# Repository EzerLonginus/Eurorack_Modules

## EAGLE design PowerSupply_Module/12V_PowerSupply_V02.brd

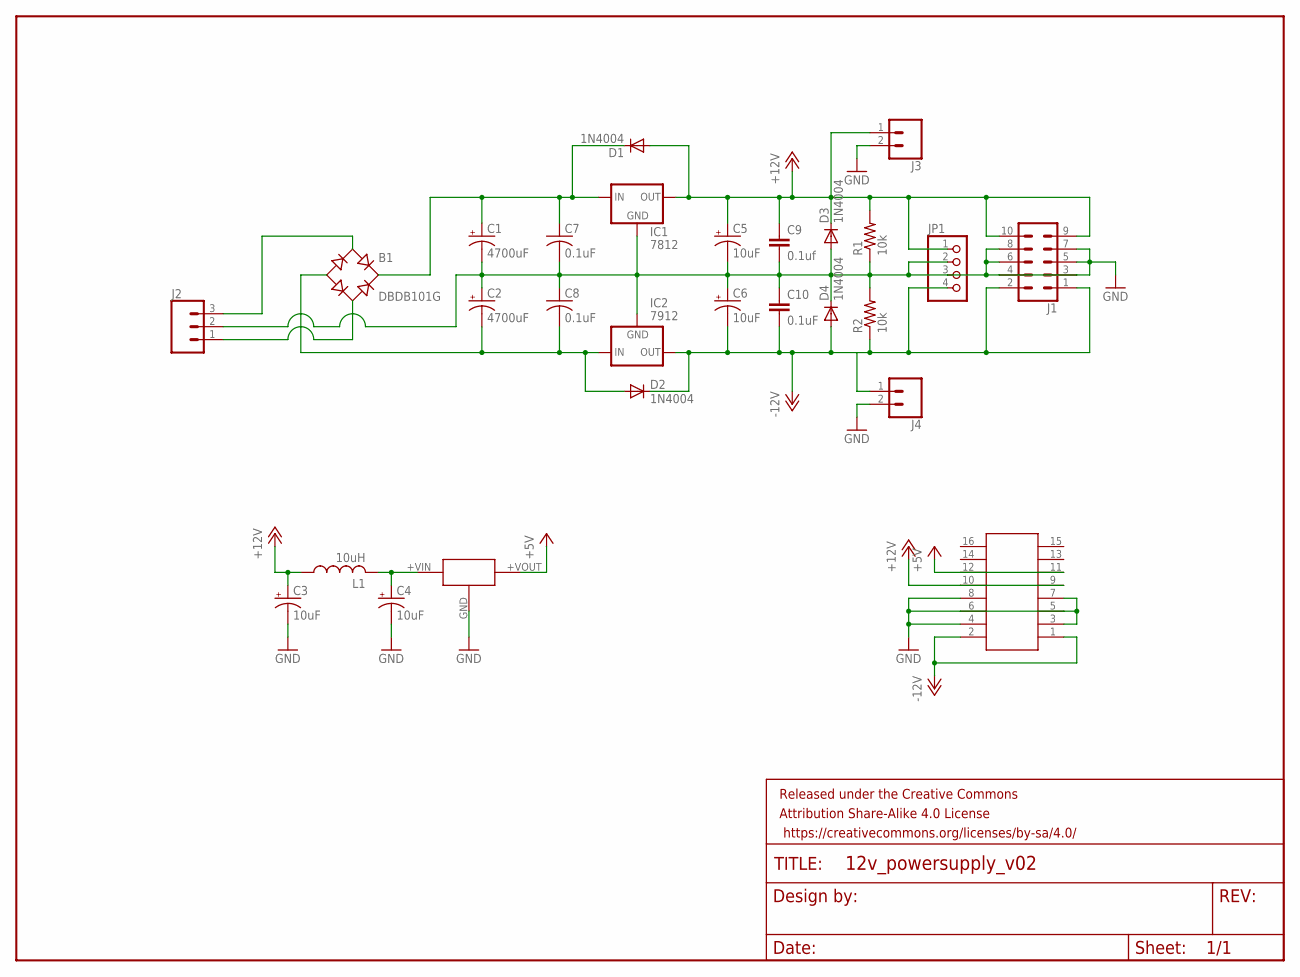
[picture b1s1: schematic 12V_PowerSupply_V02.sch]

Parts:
B1: DBDB101G; DB
C1, C2: 4700uF; E7,5-18
C3, C4, C5, C6: 10uF; E2,5-7
C7, C8: 0.1uF; C150-054X183
C9: 0.1uf; C050-025X075
C10: 0.1uF; C050-025X075
D1, D2, D3, D4: 1N4004; DO41-10
FRAME1: FRAME-LETTER; CREATIVE_COMMONS
IC1: 7812; 78XXS
IC2: 7912; 79XXS
J1: CONN_05X2SHD; 2X5-SHROUDED
J2: CONN_03-SCREW-5MM; SCREWTERMINAL-5MM-3
J3, J4: CONN_023.5MM-NO_SILK; SCREWTERMINAL-3.5MM-2-NS
JP1: PINHD-1X4; 1X04
L1: 10uH; 6000-XXXX-RC
R1, R2: 10k; 0204/7
U$1: 8X2_HEADER_SHROUDED
U$2: R_78E_5V; R_78E

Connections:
+5V: U$1.11, U$1.12, U$2.+VOUT
+12V: C3.+, C5.+, C9.1, D1.A, D3.C, IC1.OUT, J1.9, J1.10, J3.1, JP1.1, L1.1, R1.2, U$1.9, U$1.10
-12V: C6.-, C10.2, D2.C, D4.A, IC2.OUT, J1.1, J1.2, J4.1, JP1.4, R2.1, U$1.1, U$1.2
GND: C1.-, C2.+, C3.-, C4.-, C5.-, C6.+, C7.2, C8.1, C9.2, C10.1, D3.A, D4.C, IC1.GND, IC2.GND, J1.3, J1.4, J1.5, J1.6, J1.7, J1.8, J2.2, J3.2, J4.2, JP1.2, JP1.3, R1.1, R2.2, U$1.3, U$1.4, U$1.5, U$1.6, U$1.7, U$1.8, U$2.GND
unnamed: C4.+, L1.2, U$2.+VIN
unnamed: B1.+, C1.+, C7.1, D1.C, IC1.IN
unnamed: B1.-, C2.-, C8.2, D2.A, IC2.IN
unnamed: B1.AC1, J2.3
unnamed: B1.AC2, J2.1

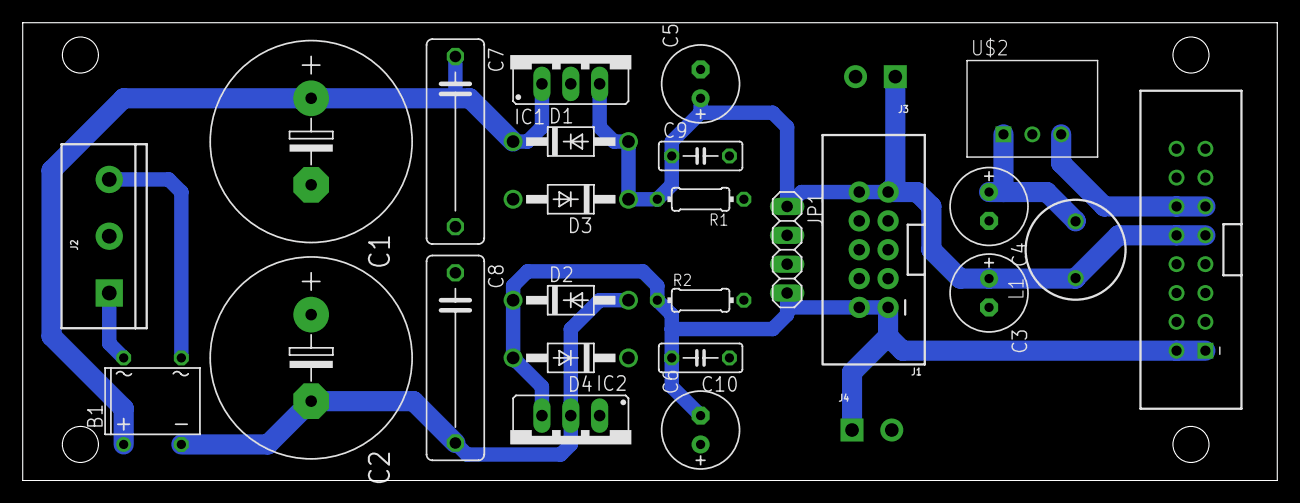
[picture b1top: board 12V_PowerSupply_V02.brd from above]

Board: 2 copper layers, 110.5 x 40.3 mm, 28 parts (0 on the bottom side), 9 nets.

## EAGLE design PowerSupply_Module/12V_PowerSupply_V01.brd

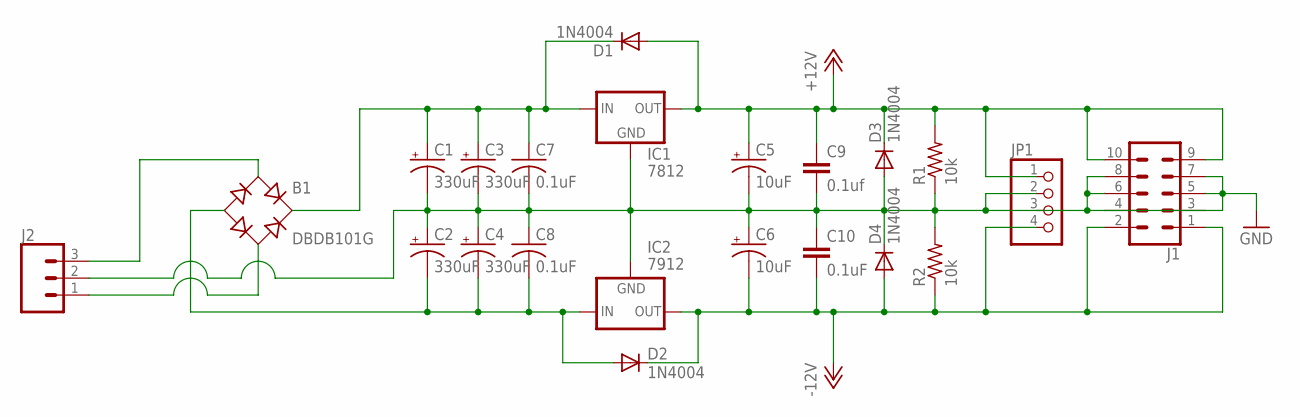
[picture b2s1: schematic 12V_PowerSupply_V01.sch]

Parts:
B1: DBDB101G; DB
C1, C2, C3, C4: 330uF; E7,5-18
C5, C6: 10uF; E2,5-7
C7, C8: 0.1uF; C150-054X183
C9: 0.1uf; C050-025X075
C10: 0.1uF; C050-025X075
D1, D2, D3, D4: 1N4004; DO41-10
IC1: 7812; 78XXS
IC2: 7912; 79XXS
J1: CONN_05X2SHD; 2X5-SHROUDED
J2: CONN_03-SCREW-5MM; SCREWTERMINAL-5MM-3
JP1: PINHD-1X4; 1X04
R1, R2: 10k; 0204/7

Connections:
+12V: C5.+, C9.1, D1.A, D3.C, IC1.OUT, J1.9, J1.10, JP1.1, R1.2
-12V: C6.-, C10.2, D2.C, D4.A, IC2.OUT, J1.1, J1.2, JP1.4, R2.1
GND: C1.-, C2.+, C3.-, C4.+, C5.-, C6.+, C7.2, C8.1, C9.2, C10.1, D3.A, D4.C, IC1.GND, IC2.GND, J1.3, J1.4, J1.5, J1.6, J1.7, J1.8, J2.2, JP1.2, JP1.3, R1.1, R2.2
unnamed: B1.+, C1.+, C3.+, C7.1, D1.C, IC1.IN
unnamed: B1.-, C2.-, C4.-, C8.2, D2.A, IC2.IN
unnamed: B1.AC1, J2.3
unnamed: B1.AC2, J2.1

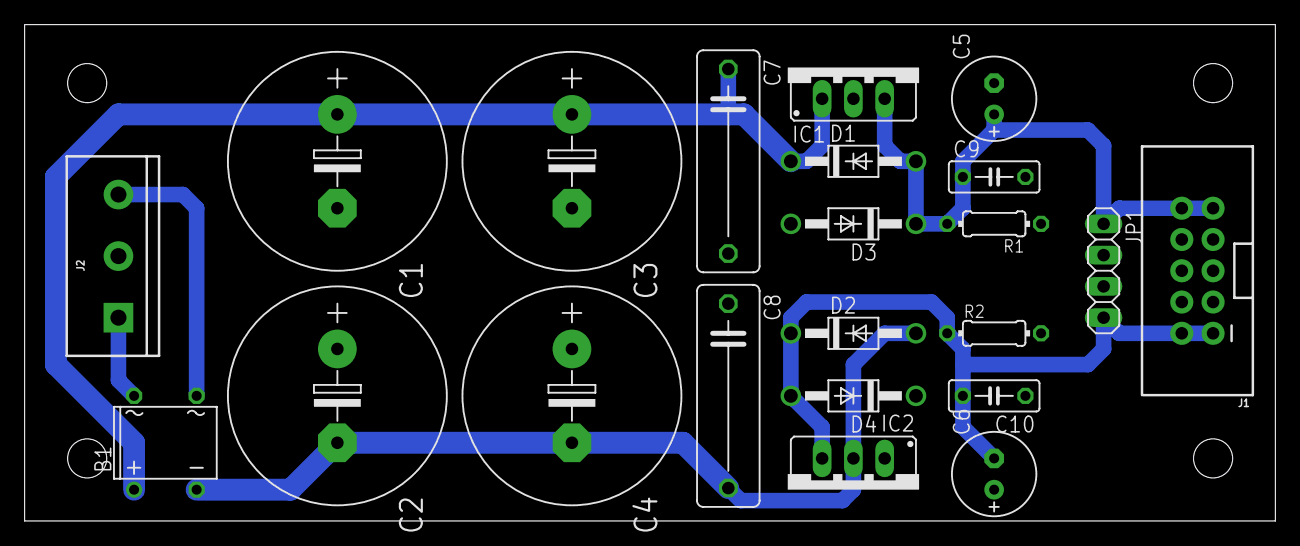
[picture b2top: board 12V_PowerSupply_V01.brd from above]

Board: 2 copper layers, 101.6 x 40.3 mm, 22 parts (0 on the bottom side), 7 nets.

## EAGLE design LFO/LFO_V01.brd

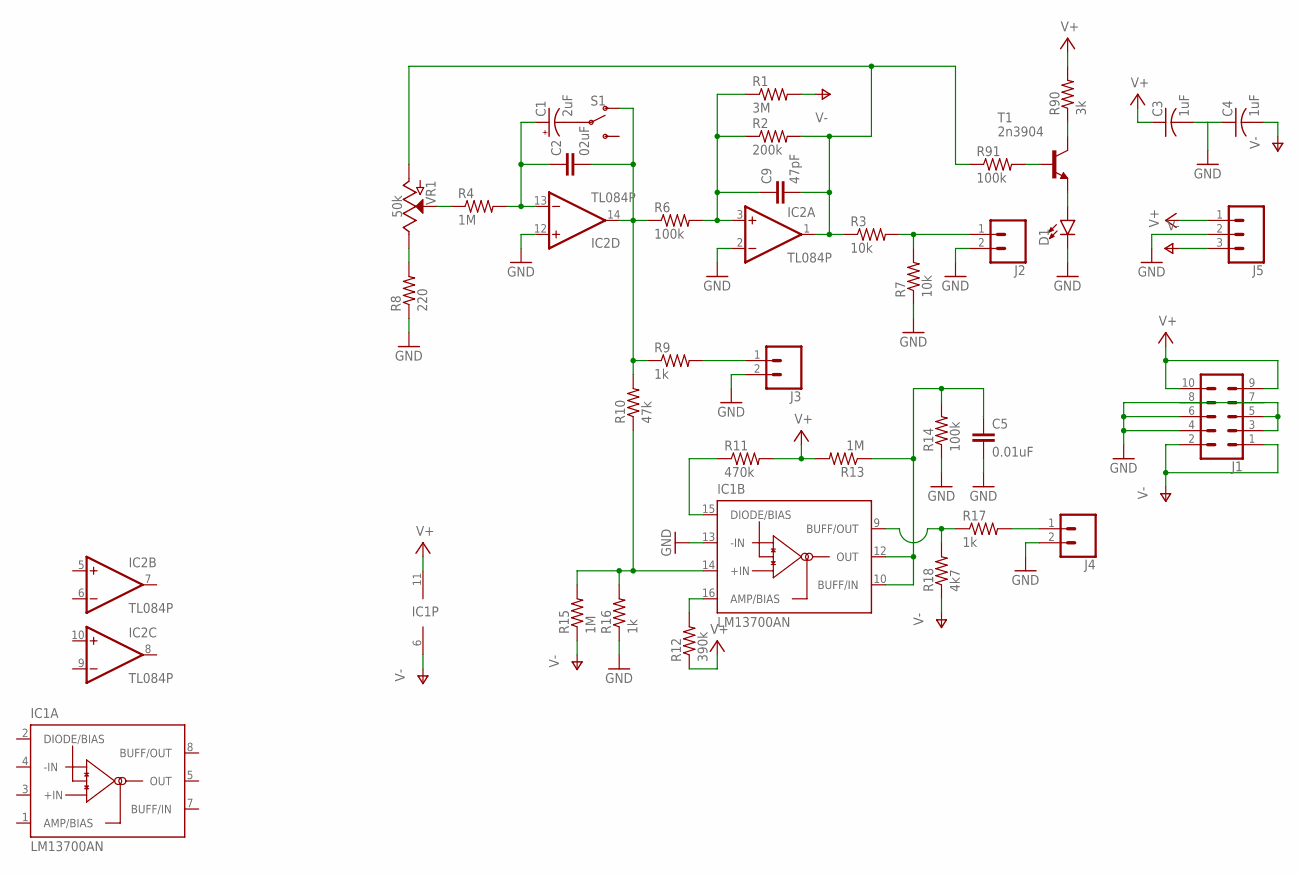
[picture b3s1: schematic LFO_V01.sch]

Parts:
C1: 2uF; E3,5-8
C2: 02uF; C050-025X075
C3, C4: 1uF; C102-043X133
C5: 0.01uF; C050-024X044
C9: 47pF; C050-025X075
D1: LED5MM-KIT; LED_5MM-KIT
IC1: LM13700AN; DIL16
IC2: TL084P; DIL14
J1: CONN_05X2SHD; 2X5-SHROUDED
J2, J3, J4: CONN_023.5MM-NO_SILK; SCREWTERMINAL-3.5MM-2-NS
J5: CONN_03-SCREW-5MM; SCREWTERMINAL-5MM-3
R1: 3M; 0204/7
R2: 200k; 0204/7
R3, R7: 10k; 0204/7
R4, R13, R15: 1M; 0204/7
R6, R14, R91: 100k; 0204/7
R8: 220; 0204/7
R9, R16, R17: 1k; 0204/7
R10: 47k; 0204/7
R11: 470k; 0204/7
R12: 390k; 0204/7
R18: 4k7; 0204/7
R90: 3k; 0204/7
S1: SWITCH-SPDT-PTH-11.6X4.0MM; SWITCH_SPDT_PTH_11.6X4.0MM
T1: 2n3904; TO92-EBC
VR1: 50k; POT-PTH-ALPS-KIT

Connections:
GND: C3.2, C4.1, C5.2, D1.K (C), IC1.13 (-IN), IC2.2 (-IN), IC2.12 (+IN), J1.3, J1.4, J1.5, J1.6, J1.7, J1.8, J2.2, J3.2, J4.2, J5.2, R7.1, R8.1, R14.1, R16.1
unnamed: C2.2, IC2.14 (OUT), R6.1, R9.1, R10.2, S1.1 (O)
unnamed: C9.1, IC2.3 (+IN), R1.1, R2.1, R6.2
unnamed: C1.+, C2.1, IC2.13 (-IN), R4.2
unnamed: C9.2, IC2.1 (OUT), R2.2, R3.1, R91.1, VR1.P$3 (A)
unnamed: C1.-, S1.2
unnamed: R91.2, T1.B
unnamed: R90.1, T1.C
unnamed: J2.1, R3.2, R7.2
unnamed: R4.1, VR1.P$2 (S)
unnamed: R8.2, VR1.P$1 (E)
unnamed: IC1.14 (+IN), R10.1, R15.2, R16.2
unnamed: D1.A, T1.E
unnamed: IC1.15 (DIODE/BIAS), R11.1
unnamed: J3.1, R9.2
unnamed: C5.1, IC1.10 (BUFF/IN), IC1.12 (OUT), R13.1, R14.2
unnamed: IC1.16 (AMP/BIAS), R12.2
unnamed: IC1.9 (BUFF/OUT), R17.1, R18.2
unnamed: J4.1, R17.2
V+: C3.1, IC1.11 (V+), IC2.4 (V+), J1.9, J1.10, J5.1, R11.2, R12.1, R13.2, R90.2
V-: C4.2, IC1.6 (V-), IC2.11 (V-), J1.1, J1.2, J5.3, R1.2, R15.1, R18.1

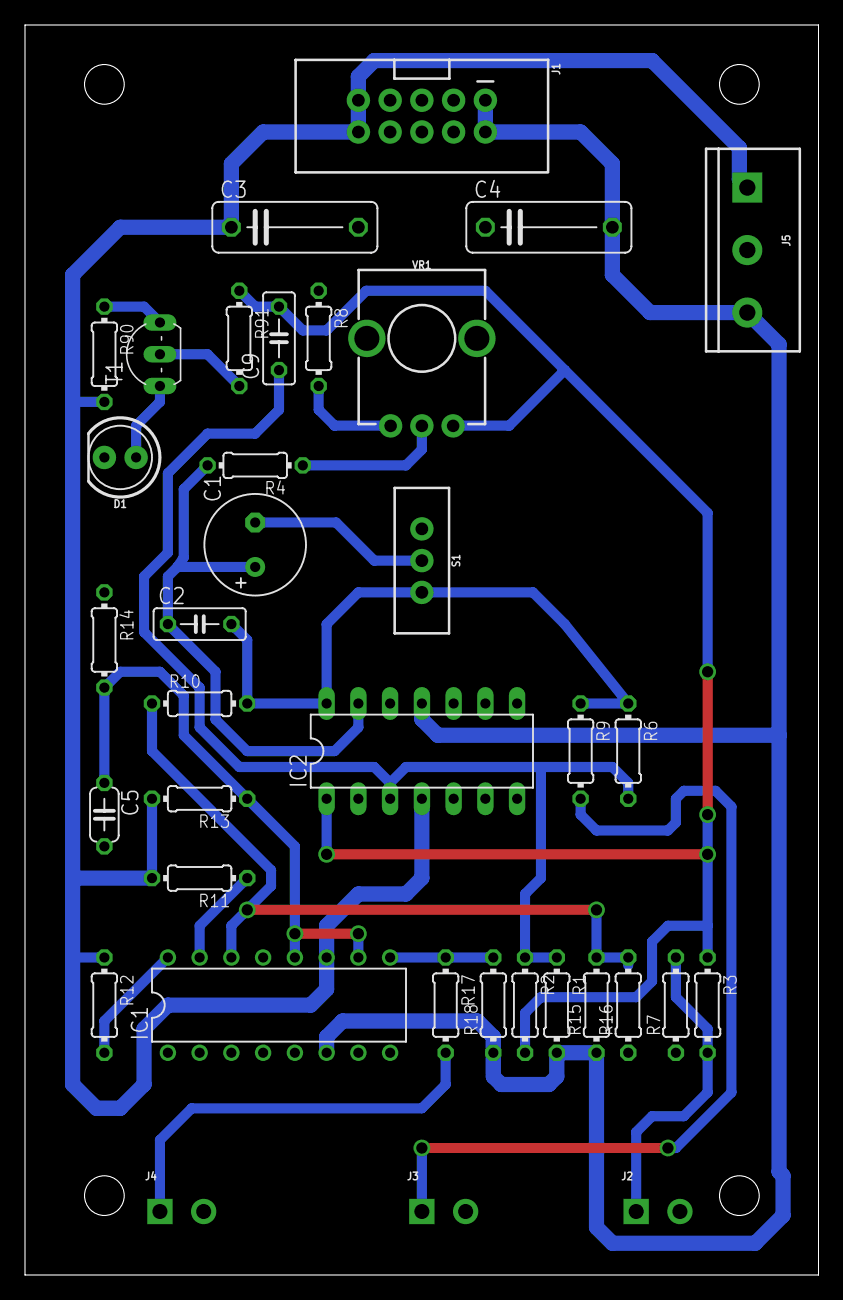
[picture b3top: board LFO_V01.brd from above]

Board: 2 copper layers, 63.5 x 100.0 mm, 36 parts (0 on the bottom side), 21 nets.

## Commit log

2018-11-27 Initial Commit
    Power Supply and LFO Eagle Boards
2018-12-05 Version 2
    Added +5V Rail, Screw 12V Screw Terminal Outputs, and removed 330uF Cap.
    Needs to be tested.

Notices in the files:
parts and their libraries:
SparkFun-Connectors: Licensing: Creative Commons ShareAlike 4.0 International - https://creativecommons.org/licenses/by-sa/4.0
SparkFun-Aesthetics: Released under the Creative Commons Attribution Share-Alike 4.0 License
SparkFun-Aesthetics: https://creativecommons.org/licenses/by-sa/4.0
